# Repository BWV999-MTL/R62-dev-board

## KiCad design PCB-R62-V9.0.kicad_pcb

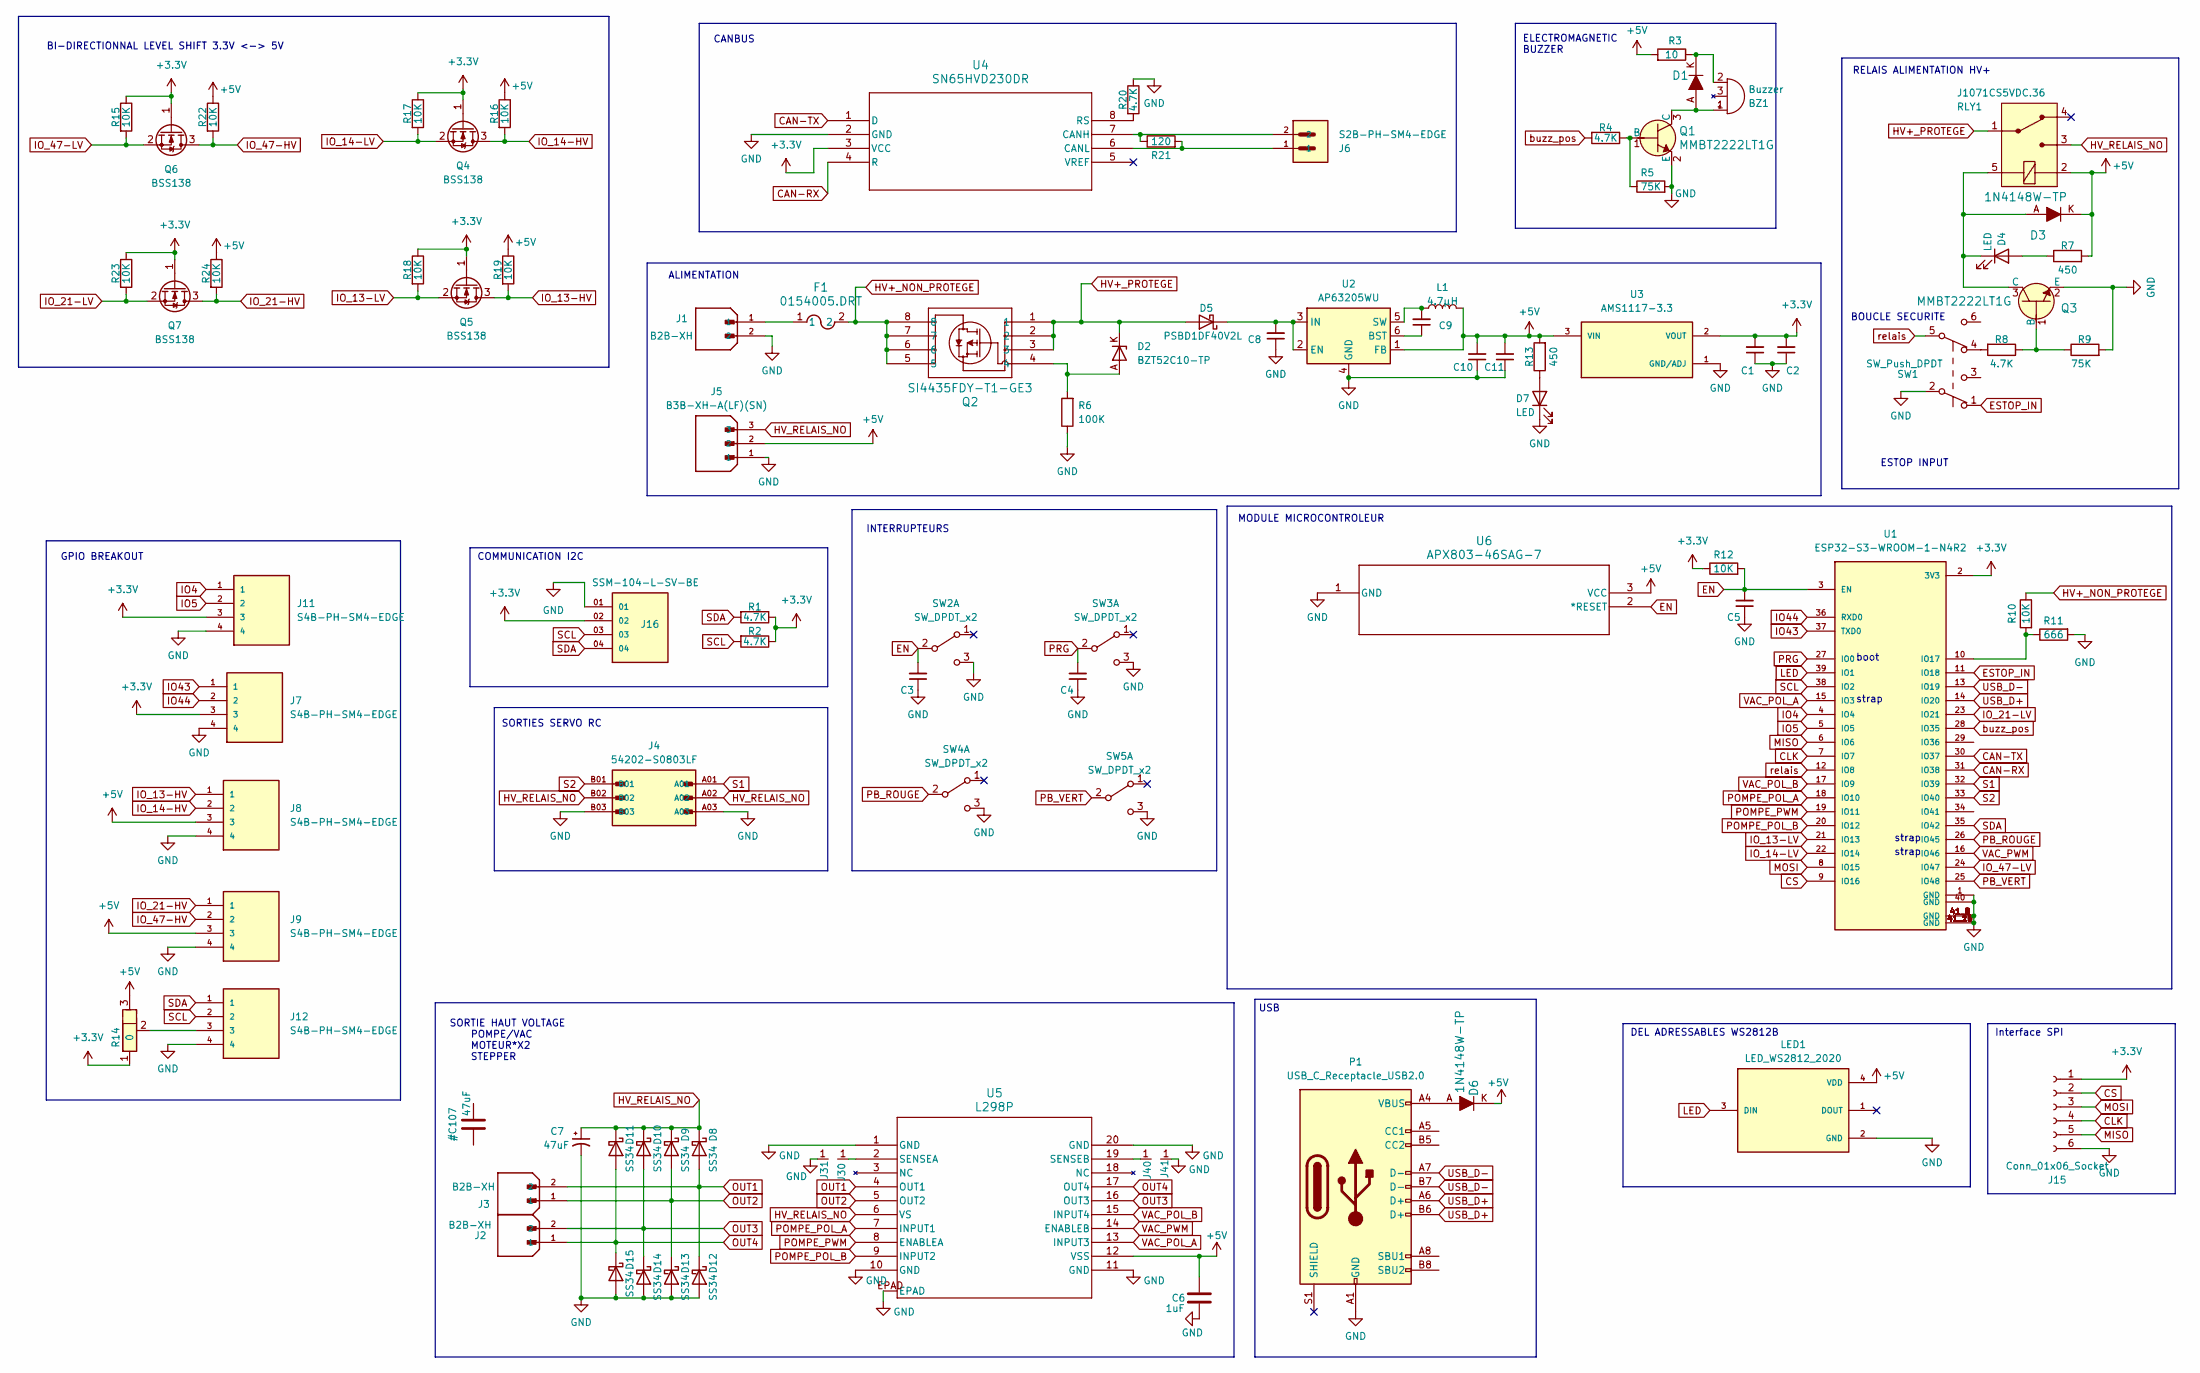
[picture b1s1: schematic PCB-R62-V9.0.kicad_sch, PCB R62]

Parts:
BZ1: Buzzer; 5020 smd buzzer
C1: 0.1uF; CONN3_S3B-XH_JST
C2, C8: 10uF; CAP_0805
C3, C4: 0.1uF; CAP_0805
C5, C6: 1uF; CAP_0805
C7: 47uF; 35TZV47M6.3X6.1
C9: 100nF; CAP_0805
C10, C11: 22uF; CAP_1210
D1: bzt; SOD123_MCC_AK; MPN 1N4148W-TP; Digi-Key_PN 1N4148WTPMSCT-ND
D2: BZT52C10-TP; SOD123_MCC_AK
D3, D6: 1N4148W-TP; SOD123_MCC_AK; MPN 1N4148W-TP; Digi-Key_PN 1N4148WTPMSCT-ND
D4, D7: LED; 150080RS75000_WRE
D5: PSBD1DF40V2L; SOD123_MCC
D8, D9, D10, D11, D12, D13, D14, D15: SS34; SOD123_MCC
F1: 0154005.DRT; 0154Series_LTF
J1: B2B-XH; JST_XH_S2B-XH-A_1x02_P2.50mm_Horizontal; PARTREV N/A
J2, J3: B2B-XH; JST_B2B-XH-A(LF)(SN) MINIMUM COURTYARD; PARTREV N/A
J4: 54202-S0803LF; AMPHENOL_54202-S0803LF; PARTREV AC
J5: B3B-XH-A(LF)(SN); CONN3_S3B-XH_JST; PARTREV N/A
J6: S2B-PH-SM4-EDGE; JST_S2B-PH-SM4-EDGE
J7, J8, J9, J11, J12: S4B-PH-SM4-EDGE; JST_S4B-PH-SM4-EDGE; PARTREV R
J15: Conn_01x06_Socket; GCT_BG300-06-X-X-A_REVC
J16: SSM-104-L-SV-BE; SAMTEC_SSM-104-L-SV-BE
J30, J31, J40, J41: Conn_01x01_Pin; PinHeader_1x1_P2.54mm
L1: 4.7µH; SL0420-4R7M
LED1: LED_WS2812_2020; LED_WS2812B2020; PARTREV 14/10/19
P1: USB_C_Receptacle_USB2.0; USB_C_Receptacle_GCT_USB4105-xx-A_16P_TopMnt_Horizontal
Q1, Q3: MMBT2222LT1G; SOT-23-3_1P4X3P040_ONS; MPN MMBT2222LT1G; Digi-Key_PN MMBT2222LT1GOSCT-ND
Q2: SI4435FDY-T1-GE3; SO-8_VIS
Q4, Q5, Q6, Q7: BSS138; SOT-23-3_1P4X3P040_ONS
R1, R2, R4, R8, R20: 4.7K; RES_0805
R3: 10; RES_0805
R5, R9: 75K; RES_0805
R6: 100K; RES_0805
R7, R13: 450; RES_0805
R10, R12, R15, R16, R17, R18, R19, R22, R23, R24: 10K; RES_0805
R11: 666; RES_0805
R14: 0; R_0805_2012Metric_DOUBLE_JUMPER
R21: 120; RES_0805
RLY1: J1071CS5VDC.36; MPN J1071CS5VDC.36
SW1: SW_Push_DPDT; PS-22F03
SW2, SW3, SW4, SW5: SW_DPDT_x2; BTSA-N-S-5
U1: ESP32-S3-WROOM-1-N4R2; XCVR_ESP32-S3-WROOM-1-N4R2; PARTREV v1.0
U2: AP63205WU; AP63205WU-7
U3: AMS1117-3.3; AMS1117-3.3 SOT-89; PARTREV N/A
U4: SN65HVD230DR; SN65HVD
U5: L298P; PowerSO-20_STM
U6: APX803-46SAG-7; SOT-23-3_1P4X3P040_ONS

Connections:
+3.3V: C1.2, C2.2, J7.3, J11.3, J15.1, J16.02, Q4.1 (G), Q5.1 (G), Q6.1 (G), Q7.1 (G), R1.1, R2.1, R12.1, R14.1, R15.1, R17.1, R18.1, R23.1, U1.2 (3V3), U3.2 (VOUT), U4.3 (VCC)
+5V: C6.2, C10.2, C11.2, D3.K, D6.K, J5.2, J8.3, J9.3, L1.2, LED1.4 (VDD), R3.2, R7.2, R13.2, R14.3, R16.1, R19.1, R22.1, R24.1, RLY1.2 (COIL), U2.1 (FB), U3.3 (VIN), U5.12 (VSS), U6.3 (VCC)
CAN-D: U1.30 (IO37), U4.1 (D)
CAN-R: U1.31 (IO38), U4.4 (R)
CLK: J15.4, U1.7 (IO7)
CS: J15.2, U1.9 (IO16)
EN: C3.2, C5.2, R12.2, SW2.2 (B), U1.3 (EN), U6.2 (*RESET)
ESTOP_IN: SW1.1 (A), U1.11 (IO18)
GND: C1.1, C2.1, C3.1, C4.1, C5.1, C6.1, C7.2, C8.1, C10.1, C11.1, D7.1 (K), D12.2 (A), D13.2 (A), D14.2 (A), D15.2 (A), J1.2, J4.A03, J4.B03, J5.1, J7.4, J8.4, J9.4, J11.4, J12.4, J15.6, J16.01, J31.1 (Pad_1), J41.1 (Pad_1), LED1.2 (GND), P1.A1 (GND), P1.A12 (GND), P1.B1 (GND), P1.B12 (GND), Q1.2 (E), Q3.2 (E), R5.2, R6.1, R9.2, R11.2, R20.1, SW1.2 (B), SW2.3 (C), SW3.3 (C), SW4.3 (C), SW5.3 (C), U1.1 (GND), U1.40 (GND), U1.41_1 (GND), U1.41_2 (GND), U1.41_3 (GND), U1.41_4 (GND), U1.41_5 (GND), U1.41_6 (GND), U1.41_7 (GND), U1.41_8 (GND), U1.41_9 (GND), U1.41_10 (GND), U1.41_11 (GND), U1.41_12 (GND), U1.41_13 (GND), U1.41_14 (GND), U1.41_15 (GND), U1.41_16 (GND), U1.41_17 (GND), U1.41_18 (GND), U1.41_19 (GND), U1.41_20 (GND), U1.41_21 (GND), U2.4 (GND), U3.1 (GND/ADJ), U4.2 (GND), U5.1 (GND), U5.10 (GND), U5.11 (GND), U5.20 (GND), U5.EPAD, U6.1 (GND)
HV+_NON_PROTEGE: F1.2, Q2.5, Q2.6, Q2.7, Q2.8, R10.1
HV+_PROTEGE: D2.K, D5.2 (A), Q2.1, Q2.2, Q2.3, RLY1.1 (COM)
HV_RELAIS_NO: C7.1, D8.1 (K), D9.1 (K), D10.1 (K), D11.1 (K), J4.A02, J4.B02, J5.3, RLY1.3 (NO), U5.6 (VS)
IO4: J11.1, U1.4 (IO4)
IO5: J11.2, U1.5 (IO5)
IO43: J7.1, U1.37 (TXD0)
IO44: J7.2, U1.36 (RXD0)
IO_13-HV: J8.1, Q5.3 (D), R19.2
IO_13-LV: Q5.2 (S), R18.2, U1.21 (IO13)
IO_14-HV: J8.2, Q4.3 (D), R16.2
IO_14-LV: Q4.2 (S), R17.2, U1.22 (IO14)
IO_21-HV: J9.1, Q7.3 (D), R24.2
IO_21-LV: Q7.2 (S), R23.2, U1.23 (IO21)
IO_47-HV: J9.2, Q6.3 (D), R22.2
IO_47-LV: Q6.2 (S), R15.2, U1.24 (IO47)
LED: LED1.3 (DIN), U1.39 (IO1)
MISO: J15.5, U1.6 (IO6)
MOSI: J15.3, U1.8 (IO15)
unnamed: BZ1.2 (+), D1.K, R3.1
unnamed: BZ1.1 (-), D1.A, Q1.3 (C)
unnamed: D2.A, Q2.4, R6.2
unnamed: D4.2 (A), R7.1
unnamed: D3.A, D4.1 (K), Q3.3 (C), RLY1.5 (COIL)
unnamed: C8.2, D5.1 (K), U2.2 (EN), U2.3 (IN)
unnamed: D6.A, P1.A4 (VBUS), P1.A9 (VBUS), P1.B4 (VBUS), P1.B9 (VBUS)
unnamed: D7.2 (A), R13.1
unnamed: F1.1, J1.1
unnamed: J12.3, R14.2
unnamed: Q1.1 (B), R4.1, R5.1
unnamed: Q3.1 (B), R8.1, R9.1
unnamed: R8.2, SW1.4 (A)
unnamed: R10.2, R11.1, U1.10 (IO17)
unnamed: C9.1, U2.6 (BST)
unnamed: C9.2, L1.1, U2.5 (SW)
unnamed: J6.2, R21.1, U4.7 (CANH)
unnamed: J6.1, R21.2, U4.6 (CANL)
unnamed: R20.2, U4.8 (RS)
unnamed: J30.1 (Pad_1), U5.2 (SENSEA)
unnamed: J40.1 (Pad_1), U5.19 (SENSEB)
OUT1: D8.2 (A), D12.1 (K), J3.2, U5.4 (OUT1)
OUT2: D9.2 (A), D13.1 (K), J3.1, U5.5 (OUT2)
OUT3: D10.2 (A), D14.1 (K), J2.2, U5.16 (OUT3)
OUT4: D11.2 (A), D15.1 (K), J2.1, U5.17 (OUT4)
PB_ROUGE: SW4.2 (B), U1.26 (IO45)
PB_VERT: SW5.2 (B), U1.25 (IO48)
POMPE_POL_A: U1.18 (IO10), U5.7 (INPUT1)
POMPE_POL_B: U1.20 (IO12), U5.9 (INPUT2)
POMPE_PWM: U1.19 (IO11), U5.8 (ENABLEA)
PRG: C4.2, SW3.2 (B), U1.27 (IO0)
S1: J4.A01, U1.32 (IO39)
S2: J4.B01, U1.33 (IO40)
SCL: J12.2, J16.03, R2.2, U1.38 (IO2)
SDA: J12.1, J16.04, R1.2, U1.35 (IO42)
USB_D+: P1.A6 (D+), P1.B6 (D+), U1.14 (IO20)
USB_D-: P1.A7 (D-), P1.B7 (D-), U1.13 (IO19)
VAC_POL_A: U1.15 (IO3), U5.13 (INPUT3)
VAC_POL_B: U1.17 (IO9), U5.15 (INPUT4)
VAC_PWM: U1.16 (IO46), U5.14 (ENABLEB)
buzz_pos: R4.2, U1.28 (IO35)
relais: SW1.5 (B), U1.12 (IO8)

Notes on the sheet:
BOUCLE SECURITE
ALIMENTATION
INTERRUPTEURS
strap
SORTIES SERVO RC
ELECTROMAGNETIC BUZZER
GPIO BREAKOUT
Interface SPI
USB
BI-DIRECTIONNAL LEVEL SHIFT 3.3V <-> 5V
DEL ADRESSABLES WS2812B
MODULE MICROCONTROLEUR
ESTOP INPUT
boot
COMMUNICATION I2C
SORTIE HAUT VOLTAGE POMPE/VAC MOTEUR*X2 STEPPER
RELAIS ALIMENTATION HV+
CANBUS

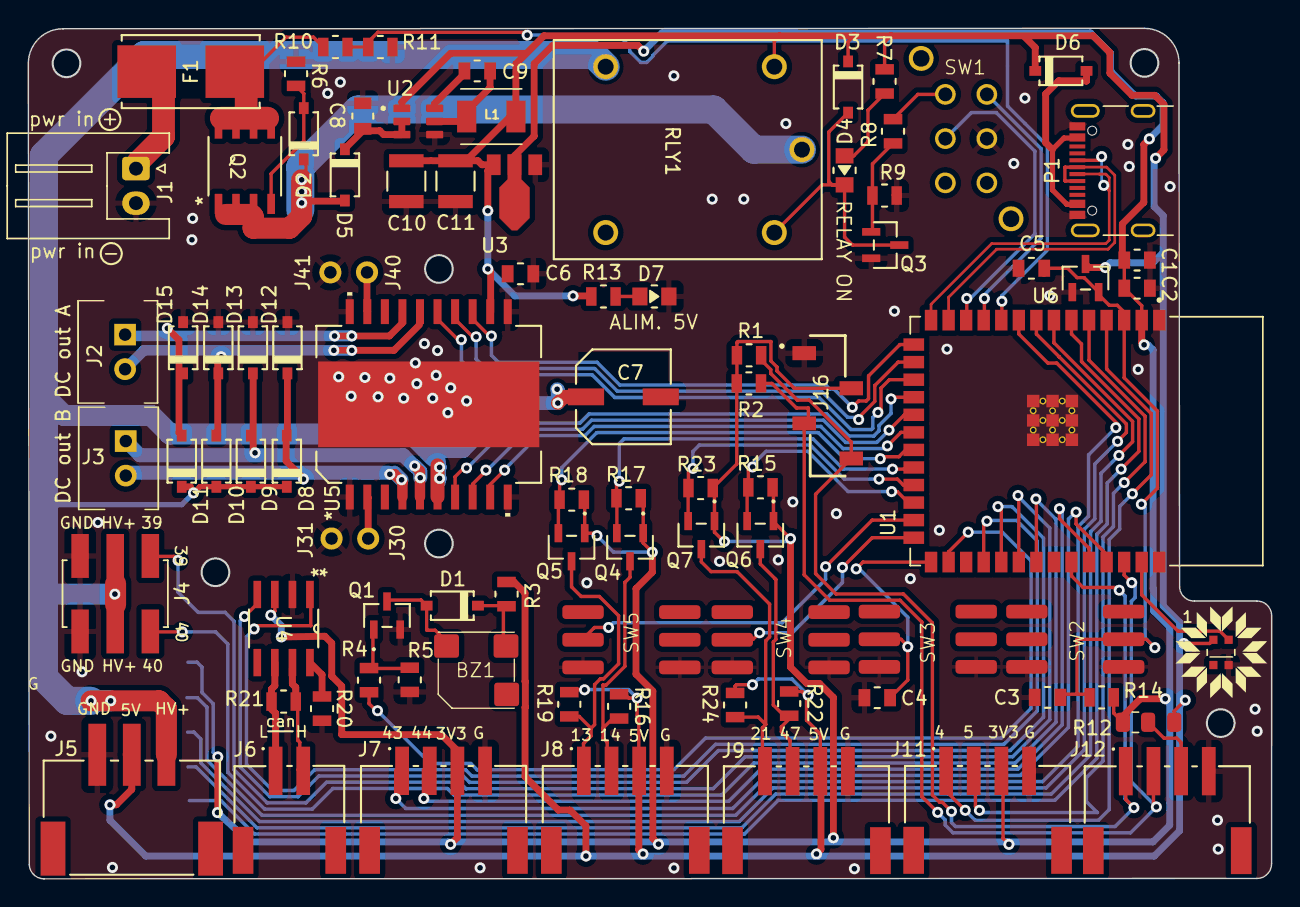
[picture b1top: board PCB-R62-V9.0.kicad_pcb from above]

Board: 2 copper layers, 89.9 x 61.5 mm, 91 parts (1 on the bottom side), 69 nets.
